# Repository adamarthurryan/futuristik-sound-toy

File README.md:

noise-and-light-synth
=====================

A simple noise synth with oscillators and feedback through flashing LEDS. Was presented in a series of workshops in Montreal, 2010 - 2012.

See documentation of the workshops here: http://madanworb.com/blog/2013/01/16/bleeps-workshop/

# Files:

- boards/sheet.png - a ready-to-burn 4 board layout (suitable for transferring to a 6"x4" photosensitive copper board) with some cool imagery built into the copper ground plane
- boards/a v2 traces plane.png - a ready-to-burn single board layout with a boring old ground plane
- docs/kit insert.png & docs/description.rtf - handout materials for the Eastern Block workshop, Montreal, 2012
- docs/layout.pdf - a stuffing diagram
- docs/schematic.pdf - the circuit diagram
- docs/digikey order.txt - a sample BOM for 23 complete kits
- eagle/project - the eagle project files

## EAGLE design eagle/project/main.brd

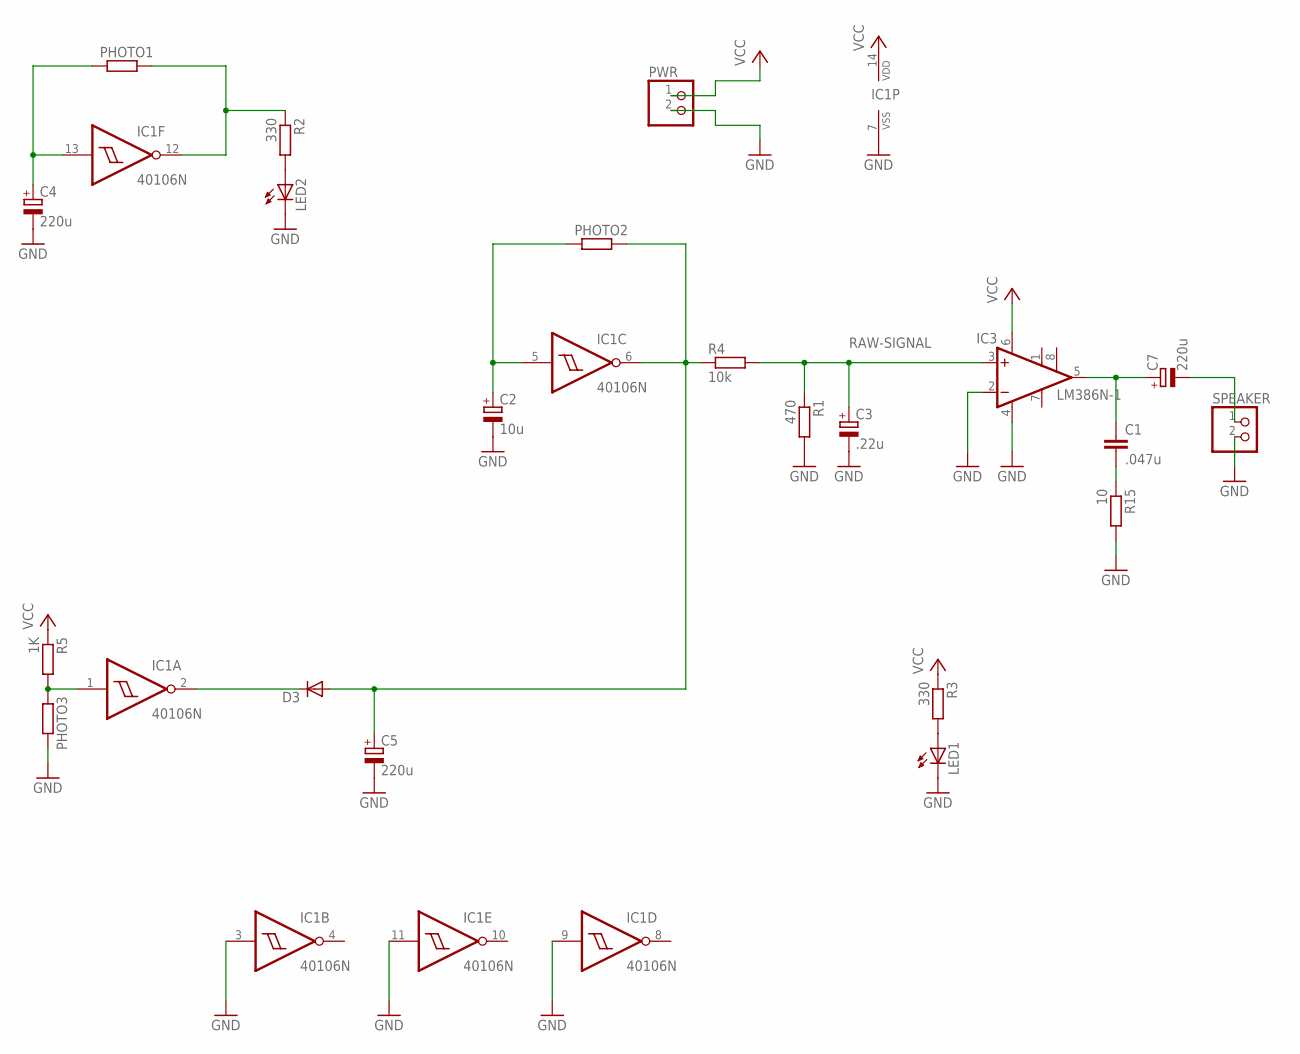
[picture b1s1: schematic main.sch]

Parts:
C1: .047u; C025-025X050
C2: 10u; TT2D6
C3: .22u; TT2D6
C4, C5, C7: 220u; TT2D6
D3: DIODE-DO35-10; DO35-10
IC1: 40106N; DIL14
IC3: LM386N-1; DIL08
LED1, LED2: LED5MM
PHOTO1, PHOTO2, PHOTO3: R-EU_0207/5V; 0207/5V
PWR: PINHD-1X2STRAIGHT; 1X02
R1: 470; 0207/10
R2, R3: 330; 0207/10
R4: 10k; 0207/10
R5: 1K; 0207/10
R15: 10; 0207/10
SPEAKER: PINHD-1X2STRAIGHT; 1X02

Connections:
GND: C2.-, C3.-, C4.-, C5.-, IC1.3 (I), IC1.7 (VSS), IC1.9 (I), IC1.11 (I), IC3.2 (-IN), IC3.4 (GND), LED1.K (C), LED2.K (C), PHOTO3.2, PWR.2, R1.2, R15.2, SPEAKER.2
unnamed: LED2.A, R2.2
unnamed: C2.+, IC1.5 (I), PHOTO2.1
unnamed: C4.+, IC1.13 (I), PHOTO1.1
unnamed: LED1.A, R3.2
unnamed: IC1.12 (O), PHOTO1.2, R2.1
unnamed: IC1.1 (I), PHOTO3.1, R5.2
unnamed: C5.+, D3.A, IC1.6 (O), PHOTO2.2, R4.1
unnamed: D3.C, IC1.2 (O)
unnamed: C1.1, C7.+, IC3.5 (OUT)
unnamed: C1.2, R15.1
OUT-SIGNAL: C7.-, SPEAKER.1
RAW-SIGNAL: C3.+, IC3.3 (+IN), R1.1, R4.2
VCC: IC1.14 (VDD), IC3.6 (VS), PWR.1, R3.1, R5.1

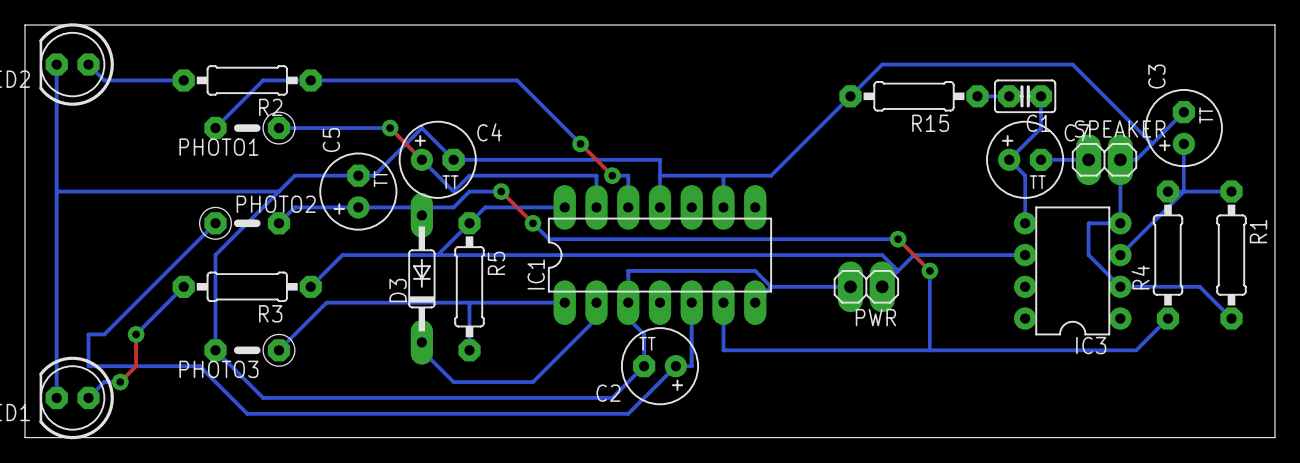
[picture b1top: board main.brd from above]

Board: 2 copper layers, 100.0 x 33.0 mm, 22 parts (0 on the bottom side), 14 nets.

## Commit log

2014-11-20 initial check in of design files
2014-11-20 updated eagle project files, added schematic rendering
2014-11-20 rename for clarity
2014-11-20 added file list to README
